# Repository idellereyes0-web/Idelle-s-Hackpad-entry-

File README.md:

# Idelle-s-Hackpad-entry-
This is my entry for the hackclub hackpad blueprint! My hackpad is simple and is used to adjust volume, open apps, and to copy/paste. BOM - 4x MX-Style switches, 4x white blank DSA keycaps 1x unsoldered Seeed XIAO RP2040, 1x EC11 Rotary encoder, 2 piece case (top and bottom).

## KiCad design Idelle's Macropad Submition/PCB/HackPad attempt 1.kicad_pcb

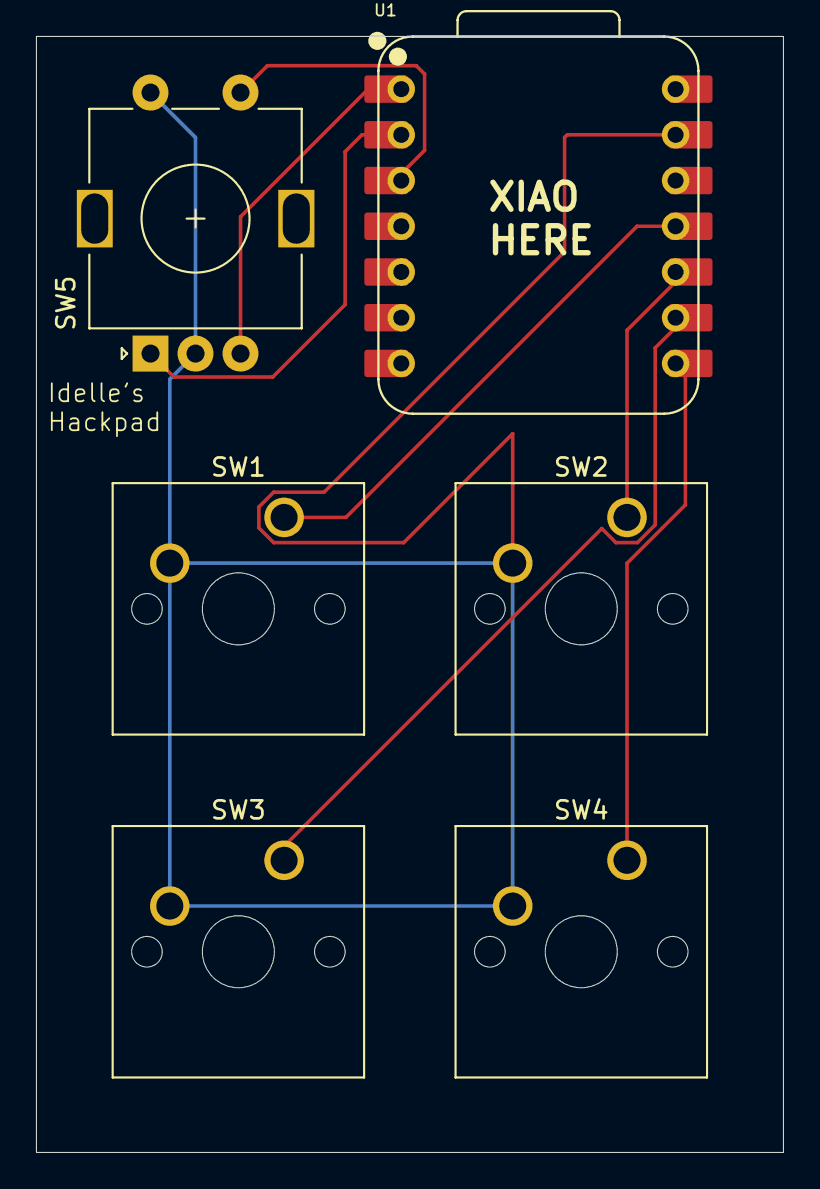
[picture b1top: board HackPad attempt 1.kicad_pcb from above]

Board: 2 copper layers, 41.5 x 62.0 mm, 6 parts (0 on the bottom side), 8 nets.

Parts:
SW1, SW2, SW3, SW4: SW_Push; SW_Cherry_MX_1.00u_PCB
SW5: RotaryEncoder_Switch; RotaryEncoder_Alps_EC11E-Switch_Vertical_H20mm
U1: XIAO-RP2040-SMD; XIAO-RP2040-DIP

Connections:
/A: SW5.A, U1.2 (GPIO27_A1_D1)
/B: SW5.B, U1.1 (GPIO26_A0_D0)
/S1: SW5.S1, U1.3 (GPIO28_A2_D2)
/SW1: SW1.1, U1.11 (GPIO3_D10_MOSI)
/SW2: SW2.1, U1.10 (GPIO4_D9_MISO)
/SW3: SW3.1, U1.9 (GPIO2_D8_SCK)
/SW4: SW4.1, U1.8 (GPIO1_D7_CSn_RX)
GND: SW1.2, SW2.2, SW3.2, SW4.2, SW5.C, SW5.S2, U1.13 (GND)

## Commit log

2026-02-22 Add new screenshot to README
2026-02-22 Add additional screenshot to README
